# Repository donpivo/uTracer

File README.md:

Project description: https://retronics.no/tag/utracer/

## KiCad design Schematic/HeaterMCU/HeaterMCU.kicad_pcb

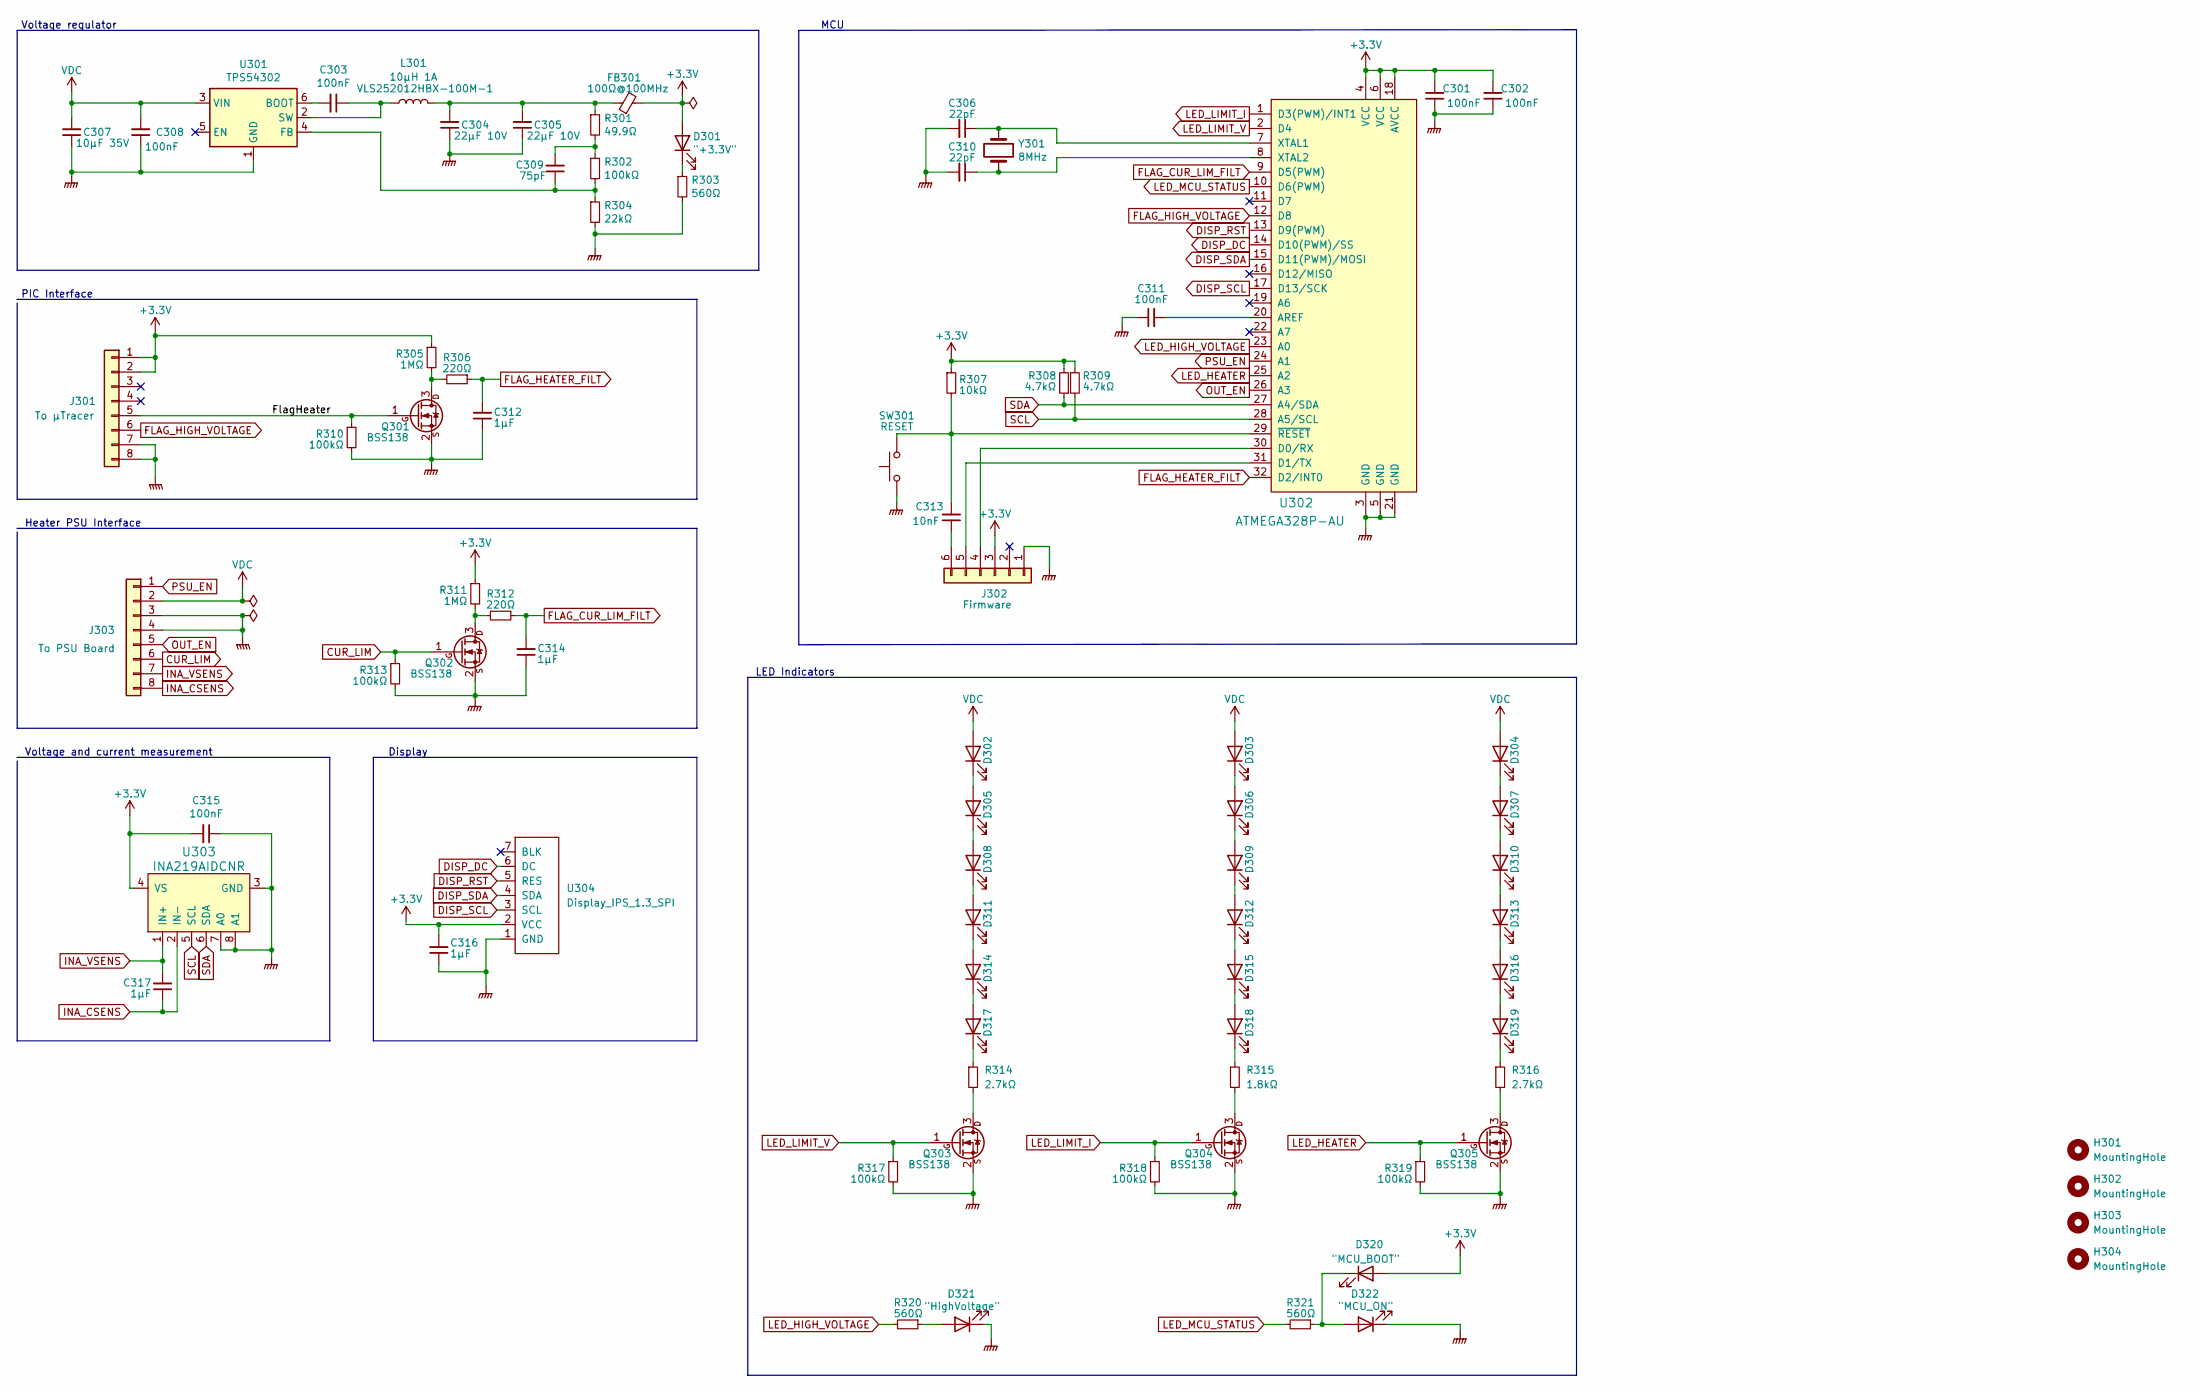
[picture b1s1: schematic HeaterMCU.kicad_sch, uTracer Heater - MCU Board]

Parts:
C301, C302, C303, C308, C311, C315: 100nF; C_0603_1608Metric_Pad1.08x0.95mm_HandSolder
C304, C305: 22µF 10V; C_0603_1608Metric_Pad1.08x0.95mm_HandSolder
C306, C310: 22pF; C_0603_1608Metric_Pad1.08x0.95mm_HandSolder
C307: 10µF 35V; C_0603_1608Metric_Pad1.08x0.95mm_HandSolder
C309: 75pF; C_0603_1608Metric_Pad1.08x0.95mm_HandSolder
C312, C314, C316, C317: 1µF; C_0603_1608Metric_Pad1.08x0.95mm_HandSolder
C313: 10nF; C_0603_1608Metric_Pad1.08x0.95mm_HandSolder
D301: "+3.3V"; LED_0603_1608Metric_Pad1.05x0.95mm_HandSolder
D302, D305, D308, D311, D314, D317: "Voltage limit"; LED_0603_1608Metric_Pad1.05x0.95mm_HandSolder
D303, D306, D309, D312, D315, D318: "Current limit"; LED_0603_1608Metric_Pad1.05x0.95mm_HandSolder
D304, D307, D310, D313, D316, D319: "Heater"; LED_0603_1608Metric_Pad1.05x0.95mm_HandSolder
D320: "MCU_BOOT"; LED_0603_1608Metric_Pad1.05x0.95mm_HandSolder
D321: "HighVoltage"; LED_0603_1608Metric_Pad1.05x0.95mm_HandSolder
D322: "MCU_ON"; LED_0603_1608Metric_Pad1.05x0.95mm_HandSolder
FB301: 100Ω@100MHz; L_0603_1608Metric_Pad1.05x0.95mm_HandSolder
H301, H302, H303, H304: MountingHole; MountingHole_3.2mm_M3
J301: To µTracer; 0527450897
J302: Firmware; PinHeader_1x06_P2.54mm_Vertical
J303: To PSU Board; PinHeader_1x08_P2.54mm_Vertical
L301: 10µH 1A; L_Taiyo-Yuden_NR-20xx_HandSoldering
Q301, Q302, Q303, Q304, Q305: BSS138; SOT-23
R301: 49.9Ω; R_0603_1608Metric_Pad0.98x0.95mm_HandSolder
R302, R310, R313, R317, R318, R319: 100kΩ; R_0603_1608Metric_Pad0.98x0.95mm_HandSolder
R303, R320, R321: 560Ω; R_0603_1608Metric_Pad0.98x0.95mm_HandSolder
R304: 22kΩ; R_0603_1608Metric_Pad0.98x0.95mm_HandSolder
R305, R311: 1MΩ; R_0603_1608Metric_Pad0.98x0.95mm_HandSolder
R306, R312: 220Ω; R_0603_1608Metric_Pad0.98x0.95mm_HandSolder
R307: 10kΩ; R_0603_1608Metric_Pad0.98x0.95mm_HandSolder
R308, R309: 4.7kΩ; R_0603_1608Metric_Pad0.98x0.95mm_HandSolder
R314, R316: 2.7kΩ; R_0603_1608Metric_Pad0.98x0.95mm_HandSolder
R315: 1.8kΩ; R_0603_1608Metric_Pad0.98x0.95mm_HandSolder
SW301: RESET; Tactile_sw_SMD_side_01
U301: TPS54302; SOT-23-6_Handsoldering
U302: ATMEGA328P-AU; TQFP-32_7x7mm
U303: INA219AIDCNR; SOT-23-8_Handsoldering; MPN INA219AIDCNR; Digi-Key_PN 296-23770-1-ND
U304: Display_IPS_1.3_SPI
Y301: 8MHz; Crystal_SMD_HC49-SD

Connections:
+3V3: C301.2, C302.2, C315.2, C316.2, D301.2 (A), D320.2 (A), FB301.2, J301.1, J301.2, J302.3, R305.1, R307.1, R308.2, R309.1, R311.1, U302.4 (VCC), U302.6 (VCC), U302.18 (AVCC), U303.4 (VS), U304.2 (VCC)
/FlagHeater: J301.5, Q301.1 (G), R310.1
CUR_LIM: J303.6, Q302.1 (G), R313.1
DISP_DC: U302.14 (D10(PWM)/SS), U304.6 (DC)
DISP_RST: U302.13 (D9(PWM)), U304.5 (RES)
DISP_SCL: U302.17 (D13/SCK), U304.3 (SCL)
DISP_SDA: U302.15 (D11(PWM)/MOSI), U304.4 (SDA)
FLAG_CUR_LIM_FILT: C314.2, R312.1, U302.9 (D5(PWM))
FLAG_HEATER_FILT: C312.2, R306.1, U302.32 (D2/INT0)
FLAG_HIGH_VOLTAGE: J301.6, U302.12 (D8)
GNDPWR: C301.1, C302.1, C304.1, C305.1, C306.2, C307.1, C308.1, C310.2, C311.1, C312.1, C314.1, C315.1, C316.1, D321.1 (K), D322.1 (K), J301.7, J301.8, J302.1, J303.3, J303.4, Q301.2 (S), Q302.2 (S), Q303.2 (S), Q304.2 (S), Q305.2 (S), R303.2, R304.2, R310.2, R313.2, R317.2, R318.2, R319.2, SW301.1, U301.1 (GND), U302.3 (GND), U302.5 (GND), U302.21 (GND), U303.3 (GND), U303.7 (A0), U303.8 (A1), U304.1 (GND)
INA_CSENS: C317.1, J303.8, U303.2 (IN-)
INA_VSENS: C317.2, J303.7, U303.1 (IN+)
LED_HEATER: Q305.1 (G), R319.1, U302.25 (A2)
LED_HIGH_VOLTAGE: R320.2, U302.23 (A0)
LED_LIMIT_I: Q304.1 (G), R318.1, U302.1 (D3(PWM)/INT1)
LED_LIMIT_V: Q303.1 (G), R317.1, U302.2 (D4)
LED_MCU_STATUS: R321.2, U302.10 (D6(PWM))
unnamed: C303.1, L301.1, U301.2 (SW)
unnamed: C303.2, U301.6 (BOOT)
unnamed: C304.2, C305.2, FB301.1, L301.2, R301.1
unnamed: C306.1, U302.7 (XTAL1), Y301.1
unnamed: C309.1, R302.2, R304.1, U301.4 (FB)
unnamed: C309.2, R301.2, R302.1
unnamed: C310.1, U302.8 (XTAL2), Y301.2
unnamed: C311.2, U302.20 (AREF)
unnamed: C313.1, J302.6
unnamed: C313.2, R307.2, SW301.2, U302.29 (~RESET)
unnamed: D301.1 (K), R303.1
unnamed: D302.1 (K), D305.2 (A)
unnamed: D303.1 (K), D306.2 (A)
unnamed: D304.1 (K), D307.2 (A)
unnamed: D305.1 (K), D308.2 (A)
unnamed: D306.1 (K), D309.2 (A)
unnamed: D307.1 (K), D310.2 (A)
unnamed: D308.1 (K), D311.2 (A)
unnamed: D309.1 (K), D312.2 (A)
unnamed: D310.1 (K), D313.2 (A)
unnamed: D311.1 (K), D314.2 (A)
unnamed: D312.1 (K), D315.2 (A)
unnamed: D313.1 (K), D316.2 (A)
unnamed: D314.1 (K), D317.2 (A)
unnamed: D315.1 (K), D318.2 (A)
unnamed: D316.1 (K), D319.2 (A)
unnamed: D317.1 (K), R314.1
unnamed: D318.1 (K), R315.1
unnamed: D319.1 (K), R316.1
unnamed: D320.1 (K), D322.2 (A), R321.1
unnamed: D321.2 (A), R320.1
unnamed: J302.4, U302.30 (D0/RX)
unnamed: J302.5, U302.31 (D1/TX)
unnamed: Q301.3 (D), R305.2, R306.2
unnamed: Q302.3 (D), R311.2, R312.2
unnamed: Q303.3 (D), R314.2
unnamed: Q304.3 (D), R315.2
unnamed: Q305.3 (D), R316.2
OUT_EN: J303.5, U302.26 (A3)
PSU_EN: J303.1, U302.24 (A1)
SCL: R309.2, U302.28 (A5/SCL), U303.5 (SCL)
SDA: R308.1, U302.27 (A4/SDA), U303.6 (SDA)
VDC: C307.2, C308.2, D302.2 (A), D303.2 (A), D304.2 (A), J303.2, U301.3 (VIN)

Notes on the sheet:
Voltage regulator
Heater PSU Interface
Display
PIC Interface
LED Indicators
MCU
Voltage and current measurement

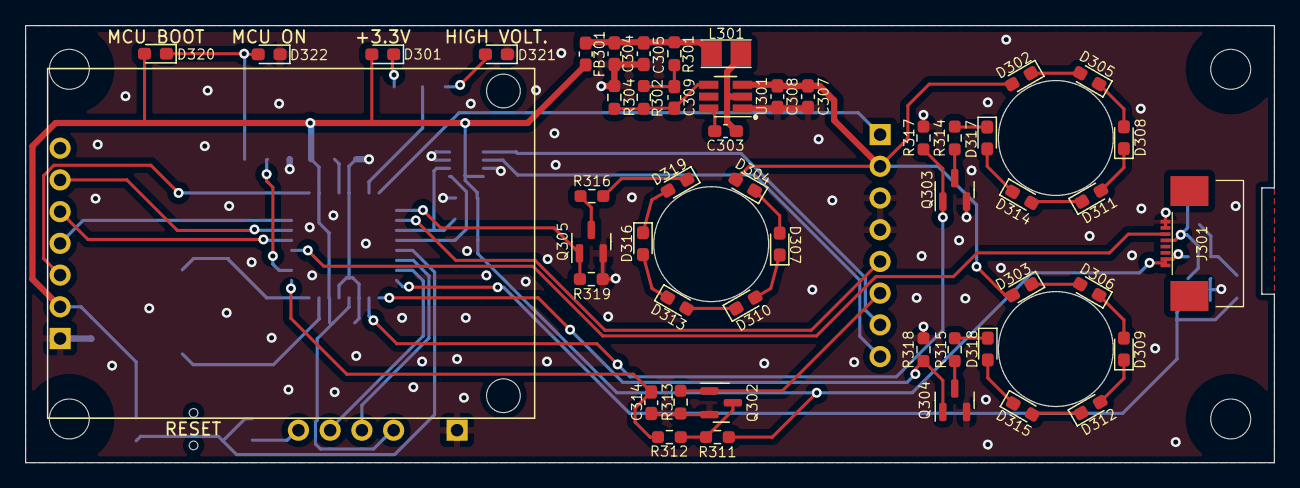
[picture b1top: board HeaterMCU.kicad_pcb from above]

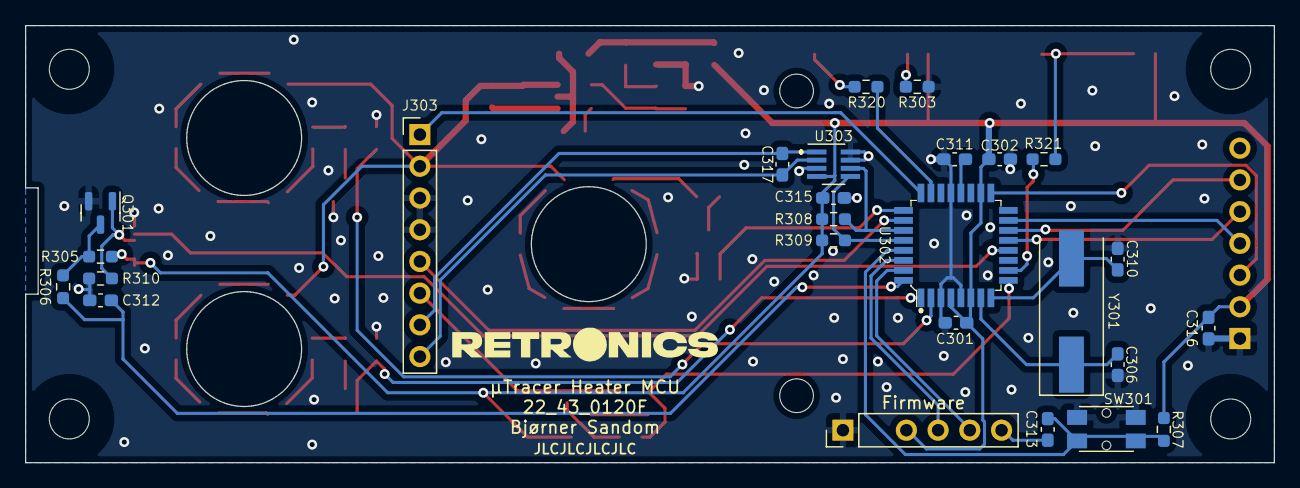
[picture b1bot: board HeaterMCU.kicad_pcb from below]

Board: 2 copper layers, 100.0 x 35.0 mm, 80 parts (26 on the bottom side), 61 nets.

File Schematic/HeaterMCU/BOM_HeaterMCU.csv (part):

"Source:","C:\Users\bjorn\OneDrive\Projects\µTracer\Schematic\HeaterMCU\HeaterMCU.kicad_sch"
"Date:","Fri May 12 07:43:41 2023"
"Tool:","Eeschema (6.0.11)"
"Generator:","C:\Program Files\KiCad\6.0\bin\scripting\plugins/bom_csv_grouped_by_value.py"
"Component Count:","80"

"Individual Components:"

"Item","Qty","Reference(s)","Value","LibPart","Footprint","Datasheet","Category","Comments","DK_Datasheet_Link","DK_Detail_Page","Description","Digi-Key_PN","Family","MPN","Manufacturer","Status"
"","","C301","100nF","Device:C_Small","Capacitor_SMD:C_0603_1608Metric_Pad1.08x0.95mm_HandSolder","~","","","","","","","","","",""
"","","C302","100nF","Device:C_Small","Capacitor_SMD:C_0603_1608Metric_Pad1.08x0.95mm_HandSolder","~","","","","","","","","","",""
"","","C303","100nF","Device:C_Small","Capacitor_SMD:C_0603_1608Metric_Pad1.08x0.95mm_HandSolder","~","","","","","","","","","",""
"","","C304","22µF 10V","Device:C_Small","Capacitor_SMD:C_0603_1608Metric_Pad1.08x0.95mm_HandSolder","~","","","","","","","","","",""
"","","C305","22µF 10V","Device:C_Small","Capacitor_SMD:C_0603_1608Metric_Pad1.08x0.95mm_HandSolder","~","","","","","","","","","",""
"","","C306","22pF","Device:C_Small","Capacitor_SMD:C_0603_1608Metric_Pad1.08x0.95mm_HandSolder","~","","","","","","","","","",""
"","","C307","10µF 35V","Device:C_Small","Capacitor_SMD:C_0603_1608Metric_Pad1.08x0.95mm_HandSolder","~","","","","","","","","","",""
"","","C308","100nF","Device:C_Small","Capacitor_SMD:C_0603_1608Metric_Pad1.08x0.95mm_HandSolder","~","","","","","","","","","",""
"","","C309","75pF","Device:C_Small","Capacitor_SMD:C_0603_1608Metric_Pad1.08x0.95mm_HandSolder","~","","","","","","","","","",""
"","","C310","22pF","Device:C_Small","Capacitor_SMD:C_0603_1608Metric_Pad1.08x0.95mm_HandSolder","~","","","","","","","","","",""
"","","C311","100nF","Device:C_Small","Capacitor_SMD:C_0603_1608Metric_Pad1.08x0.95mm_HandSolder","~","","","","","","","","","",""
"","","C312","1µF","Device:C_Small","Capacitor_SMD:C_0603_1608Metric_Pad1.08x0.95mm_HandSolder","~","","","","","","","","","",""
"","","C313","10nF","Device:C_Small","Capacitor_SMD:C_0603_1608Metric_Pad1.08x0.95mm_HandSolder","~","","","","","","","","","",""
"","","C314","1µF","Device:C_Small","Capacitor_SMD:C_0603_1608Metric_Pad1.08x0.95mm_HandSolder","~","","","","","","","","","",""
"","","C315","100nF","Device:C_Small","Capacitor_SMD:C_0603_1608Metric_Pad1.08x0.95mm_HandSolder","~","","","","","","","","","",""
"","","C316","1µF","Device:C_Small","Capacitor_SMD:C_0603_1608Metric_Pad1.08x0.95mm_HandSolder","~","","","","","","","","","",""
"","","C317","1µF","Device:C_Small","Capacitor_SMD:C_0603_1608Metric_Pad1.08x0.95mm_HandSolder","~","","","","","","","","","",""
"","","D301","""+3.3V""","Device:LED","LED_SMD:LED_0603_1608Metric_Pad1.05x0.95mm_HandSolder","~","","","","","","","","","",""
"","","D302","""Voltage limit""","Device:LED","LED_SMD:LED_0603_1608Metric_Pad1.05x0.95mm_HandSolder","~","","","","","","","","","",""
"","","D303","""Current limit""","Device:LED","LED_SMD:LED_0603_1608Metric_Pad1.05x0.95mm_HandSolder","~","","","","","","","","","",""
"","","D304","""Heater""","Device:LED","LED_SMD:LED_0603_1608Metric_Pad1.05x0.95mm_HandSolder","~","","","","","","","","","",""
"","","D305","""Voltage limit""","Device:LED","LED_SMD:LED_0603_1608Metric_Pad1.05x0.95mm_HandSolder","~","","","","","","","","","",""
"","","D306","""Current limit""","Device:LED","LED_SMD:LED_0603_1608Metric_Pad1.05x0.95mm_HandSolder","~","","","","","","","","","",""
"","","D307","""Heater""","Device:LED","LED_SMD:LED_0603_1608Metric_Pad1.05x0.95mm_HandSolder","~","","","","","","","","","",""
"","","D308","""Voltage limit""","Device:LED","LED_SMD:LED_0603_1608Metric_Pad1.05x0.95mm_HandSolder","~","","","","","","","","","",""
"","","D309","""Current limit""","Device:LED","LED_SMD:LED_0603_1608Metric_Pad1.05x0.95mm_HandSolder","~","","","","","","","","","",""
"","","D310","""Heater""","Device:LED","LED_SMD:LED_0603_1608Metric_Pad1.05x0.95mm_HandSolder","~","","","","","","","","","",""
"","","D311","""Voltage limit""","Device:LED","LED_SMD:LED_0603_1608Metric_Pad1.05x0.95mm_HandSolder","~","","","","","","","","","",""
"","","D312","""Current limit""","Device:LED","LED_SMD:LED_0603_1608Metric_Pad1.05x0.95mm_HandSolder","~","","","","","","","","","",""
"","","D313","""Heater""","Device:LED","LED_SMD:LED_0603_1608Metric_Pad1.05x0.95mm_HandSolder","~","","","","","","","","","",""
"","","D314","""Voltage limit""","Device:LED","LED_SMD:LED_0603_1608Metric_Pad1.05x0.95mm_HandSolder","~","","","","","","","","","",""
"","","D315","""Current limit""","Device:LED","LED_SMD:LED_0603_1608Metric_Pad1.05x0.95mm_HandSolder","~","","","","","","","","","",""
"","","D316","""Heater""","Device:LED","LED_SMD:LED_0603_1608Metric_Pad1.05x0.95mm_HandSolder","~","","","","","","","","","",""
"","","D317","""Voltage limit""","Device:LED","LED_SMD:LED_0603_1608Metric_Pad1.05x0.95mm_HandSolder","~","","","","","","","","","",""
"","","D318","""Current limit""","Device:LED","LED_SMD:LED_0603_1608Metric_Pad1.05x0.95mm_HandSolder","~","","","","","","","","","",""
"","","D319","""Heater""","Device:LED","LED_SMD:LED_0603_1608Metric_Pad1.05x0.95mm_HandSolder","~","","","","","","","","","",""
"","","D320","""MCU_BOOT""","Device:LED","LED_SMD:LED_0603_1608Metric_Pad1.05x0.95mm_HandSolder","~","","","","","","","","","",""
"","","D321","""HighVoltage""","Device:LED","LED_SMD:LED_0603_1608Metric_Pad1.05x0.95mm_HandSolder","~","","","","","","","","","",""
"","","D322","""MCU_ON""","Device:LED","LED_SMD:LED_0603_1608Metric_Pad1.05x0.95mm_HandSolder","~","","","","","","","","","",""
"","","FB301","100Ω@100MHz","Device:FerriteBead_Small","Inductor_SMD:L_0603_1608Metric_Pad1.05x0.95mm_HandSolder","~","","","","","","","","","",""
"","","H301","MountingHole","Mechanical:MountingHole","MountingHole:MountingHole_3.2mm_M3","~","","","","","","","","","",""
"","","H302","MountingHole","Mechanical:MountingHole","MountingHole:MountingHole_3.2mm_M3","~","","","","","","","","","",""
"","","H303","MountingHole","Mechanical:MountingHole","MountingHole:MountingHole_3.2mm_M3","~","","","","","","","","","",""
"","","H304","MountingHole","Mechanical:MountingHole","MountingHole:MountingHole_3.2mm_M3","~","","","","","","","","","",""
"","","J301","To µTracer","Connector_Generic:Conn_01x08","myDevices:0527450897","~","","","","","","","","","",""
"","","J302","Firmware","Connector_Generic:Conn_01x06","Connector_PinHeader_2.54mm:PinHeader_1x06_P2.54mm_Vertical","~","","","","","","","","","",""
"","","J303","To PSU Board","Connector_Generic:Conn_01x08","Connector_PinHeader_2.54mm:PinHeader_1x08_P2.54mm_Vertical","~","","","","","","","","","",""
"","","L301","10µH 1A","Device:L","Inductor_SMD:L_Taiyo-Yuden_NR-20xx_HandSoldering","~","","VLS252012HBX-100M-1","","","","","","","",""
"","","Q301","BSS138","myDevices:BSS138","Package_TO_SOT_SMD:SOT-23","https://www.fairchildsemi.com/datasheets/BS/BSS138.pdf","","","","","","","","","",""
"","","Q302","BSS138","myDevices:BSS138","Package_TO_SOT_SMD:SOT-23","https://www.fairchildsemi.com/datasheets/BS/BSS138.pdf","","","","","","","","","",""
"","","Q303","BSS138","myDevices:BSS138","Package_TO_SOT_SMD:SOT-23","https://www.fairchildsemi.com/datasheets/BS/BSS138.pdf","","","","","","","","","",""
"","","Q304","BSS138","myDevices:BSS138","Package_TO_SOT_SMD:SOT-23","https://www.fairchildsemi.com/datasheets/BS/BSS138.pdf","","","","","","","","","",""
"","","Q305","BSS138","myDevices:BSS138","Package_TO_SOT_SMD:SOT-23","https://www.fairchildsemi.com/datasheets/BS/BSS138.pdf","","","","","","","","","",""
"","","R301","49.9Ω","Device:R_Small","Resistor_SMD:R_0603_1608Metric_Pad0.98x0.95mm_HandSolder","~","","","","","","","","","",""
"","","R302","100kΩ","Device:R_Small","Resistor_SMD:R_0603_1608Metric_Pad0.98x0.95mm_HandSolder","~","","","","","","","","","",""
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
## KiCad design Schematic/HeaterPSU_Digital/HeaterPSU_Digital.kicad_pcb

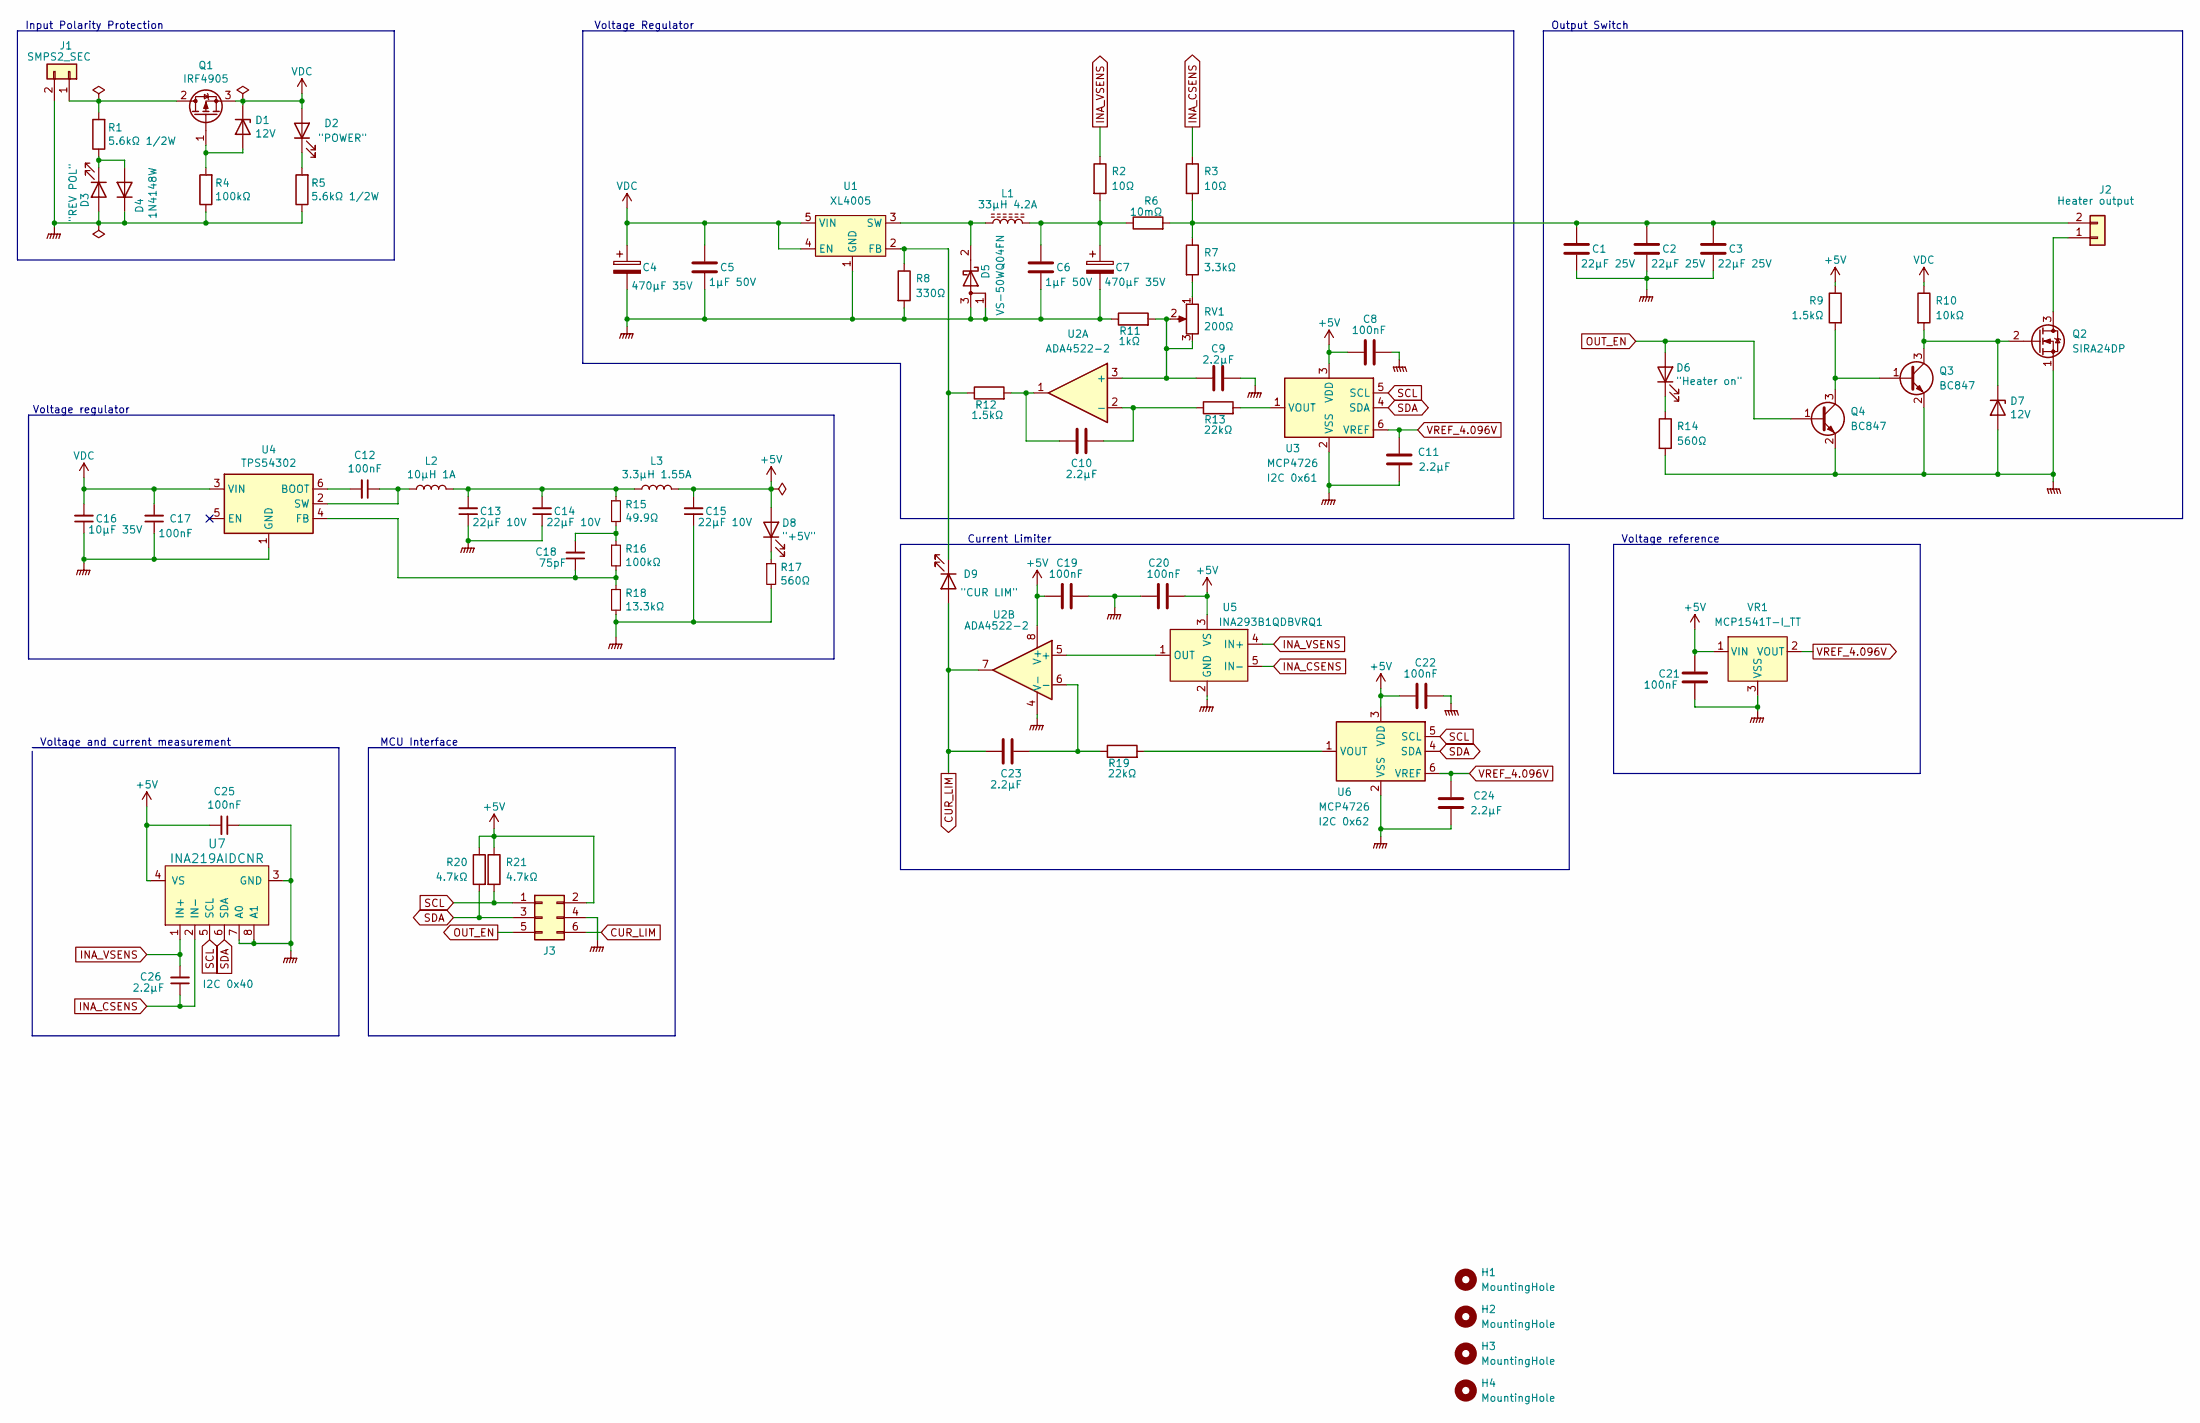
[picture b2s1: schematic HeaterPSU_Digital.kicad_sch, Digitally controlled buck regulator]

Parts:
C1, C2, C3: 22µF 25V; C_0805_2012Metric_Pad1.18x1.45mm_HandSolder
C4, C7: 470µF 35V; CP_Elec_8x10
C5, C6: 1µF 50V; C_0805_2012Metric_Pad1.18x1.45mm_HandSolder
C8, C12, C17, C19, C20, C21, C22, C25: 100nF; C_0603_1608Metric_Pad1.08x0.95mm_HandSolder
C9, C10, C11, C23, C24, C26: 2.2µF; C_0603_1608Metric_Pad1.08x0.95mm_HandSolder
C13, C14, C15: 22µF 10V; C_0603_1608Metric_Pad1.08x0.95mm_HandSolder
C16: 10µF 35V; C_0603_1608Metric_Pad1.08x0.95mm_HandSolder
C18: 75pF; C_0603_1608Metric_Pad1.08x0.95mm_HandSolder
D1, D7: 12V; D_SOD-123
D2: "POWER"; LED_0603_1608Metric_Pad1.05x0.95mm_HandSolder
D3: "REV POL"; LED_0603_1608Metric_Pad1.05x0.95mm_HandSolder
D4: 1N4148W; D_SOD-123
D5: VS-50WQ04FN; TO-252-2
D6: "Heater on"; LED_0603_1608Metric_Pad1.05x0.95mm_HandSolder
D8: "+5V"; LED_0603_1608Metric_Pad1.05x0.95mm_HandSolder
D9: "CUR LIM"; LED_0603_1608Metric_Pad1.05x0.95mm_HandSolder
H1, H2, H3, H4: MountingHole; MountingHole_3.2mm_M3
J1: SMPS2_SEC; TerminalBlock_LCSC_P5.08mm
J2: Heater output; TerminalBlock_LCSC_P5.08mm
J3: Conn_01x06; PinSocket_2x03_P1.27mm_Vertical_SMD
L1: 33µH 4.2A; L_12x12mm_H8mm
L2: 10µH 1A; L_Taiyo-Yuden_NR-20xx_HandSoldering
L3: 3.3µH 1.55A; L_Taiyo-Yuden_NR-20xx_HandSoldering
Q1: IRF4905; TO-263-2
Q2: SIRA24DP; SIRA24DP-T1-GE3
Q3, Q4: BC847; SOT-23
R1, R5: 5.6kΩ 1/2W; R_1210_3225Metric_Pad1.30x2.65mm_HandSolder
R2, R3: 10Ω; R_0603_1608Metric_Pad0.98x0.95mm_HandSolder
R4: 100kΩ; R_0805_2012Metric_Pad1.20x1.40mm_HandSolder
R6: 10mΩ; R_2512_6332Metric_Pad1.40x3.35mm_HandSolder
R7: 3.3kΩ; R_0603_1608Metric_Pad0.98x0.95mm_HandSolder
R8: 330Ω; R_0603_1608Metric_Pad0.98x0.95mm_HandSolder
R9, R12: 1.5kΩ; R_0603_1608Metric_Pad0.98x0.95mm_HandSolder
R10: 10kΩ; R_0603_1608Metric_Pad0.98x0.95mm_HandSolder
R11: 1kΩ; R_0603_1608Metric_Pad0.98x0.95mm_HandSolder
R13, R19: 22kΩ; R_0603_1608Metric_Pad0.98x0.95mm_HandSolder
R14, R17: 560Ω; R_0603_1608Metric_Pad0.98x0.95mm_HandSolder
R15: 49.9Ω; R_0603_1608Metric_Pad0.98x0.95mm_HandSolder
R16: 100kΩ; R_0603_1608Metric_Pad0.98x0.95mm_HandSolder
R18: 13.3kΩ; R_0603_1608Metric_Pad0.98x0.95mm_HandSolder
R20, R21: 4.7kΩ; R_0603_1608Metric_Pad0.98x0.95mm_HandSolder
RV1: 200Ω; Potentiometer_TT_35W
U1: XL4005; TO-263-5_TabPin3
U2: ADA4522-2; SOIC-8_3.9x4.9mm_P1.27mm
U3, U6: MCP4726; SOT-23-6
U4: TPS54302; SOT-23-6_Handsoldering
U5: INA293B1QDBVRQ1; SOT-23-5_HandSoldering
U7: INA219AIDCNR; SOT-23-8_Handsoldering; MPN INA219AIDCNR; Digi-Key_PN 296-23770-1-ND
VR1: MCP1541T-I_TT; SOT-23-3; MPN MCP1541T-I/TT; Digi-Key_PN MCP1541T-I/TTCT-ND

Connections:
+5V: C8.2, C15.2, C19.2, C20.2, C21.2, C22.2, C25.2, D8.2 (A), J3.2, L3.2, R9.1, R20.1, R21.1, U2.8 (V+), U3.3 (VDD), U5.3 (VS), U6.3 (VDD), U7.4 (VS), VR1.1 (VIN)
CUR_LIM: C23.1, D9.2 (A), J3.6, U2.7
INA_CSENS: C26.1, R3.1, U5.5 (IN-), U7.2 (IN-)
INA_VSENS: C26.2, R2.1, U5.4 (IN+), U7.1 (IN+)
unnamed: C1.1, C2.1, C3.1, J2.2, R3.2, R6.2, R7.1
unnamed: C6.1, C7.1, L1.2, R2.2, R6.1
unnamed: C9.1, R11.2, RV1.2, RV1.3, U2.3 (+)
unnamed: C10.1, R12.2, U2.1
unnamed: C10.2, R13.1, U2.2 (-)
unnamed: C12.1, L2.1, U4.2 (SW)
unnamed: C12.2, U4.6 (BOOT)
unnamed: C13.2, C14.2, L2.2, L3.1, R15.1
unnamed: C18.1, R16.2, R18.1, U4.4 (FB)
unnamed: C18.2, R15.2, R16.1
unnamed: C23.2, R19.1, U2.6 (-)
unnamed: D1.2 (A), Q1.1 (G), R4.2
unnamed: D2.1 (K), R5.2
unnamed: D3.1 (K), D4.2 (A), R1.1
unnamed: D5.2 (K), L1.1, U1.3 (SW)
unnamed: D6.1 (K), R14.1
unnamed: D8.1 (K), R17.1
unnamed: D9.1 (K), R8.1, R12.1, U1.2 (FB)
unnamed: J1.1, Q1.2 (D), R1.2
unnamed: J2.1, Q2.3 (D)
unnamed: Q3.1 (B), Q4.3 (C), R9.2
unnamed: R7.2, RV1.1
unnamed: D7.1 (K), Q2.2 (G), Q3.3 (C), R10.2
unnamed: R13.2, U3.1 (VOUT)
unnamed: R19.2, U6.1 (VOUT)
unnamed: U2.5 (+), U5.1 (OUT)
OUT_EN: D6.2 (A), J3.5, Q4.1 (B)
SCL: J3.1, R21.2, U3.5 (SCL), U6.5 (SCL), U7.5 (SCL)
SDA: J3.3, R20.2, U3.4 (SDA), U6.4 (SDA), U7.6 (SDA)
VDC: C4.1, C5.1, C16.2, C17.2, D1.1 (K), D2.2 (A), Q1.3 (S), R10.1, U1.4 (EN), U1.5 (VIN), U4.3 (VIN)
VREF_4.096V: C11.1, C24.1, U3.6 (VREF), U6.6 (VREF), VR1.2 (VOUT)

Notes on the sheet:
Voltage regulator
Output Switch
MCU Interface
Current Limiter
Voltage Regulator
Voltage and current measurement
Input Polarity Protection
Voltage reference

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
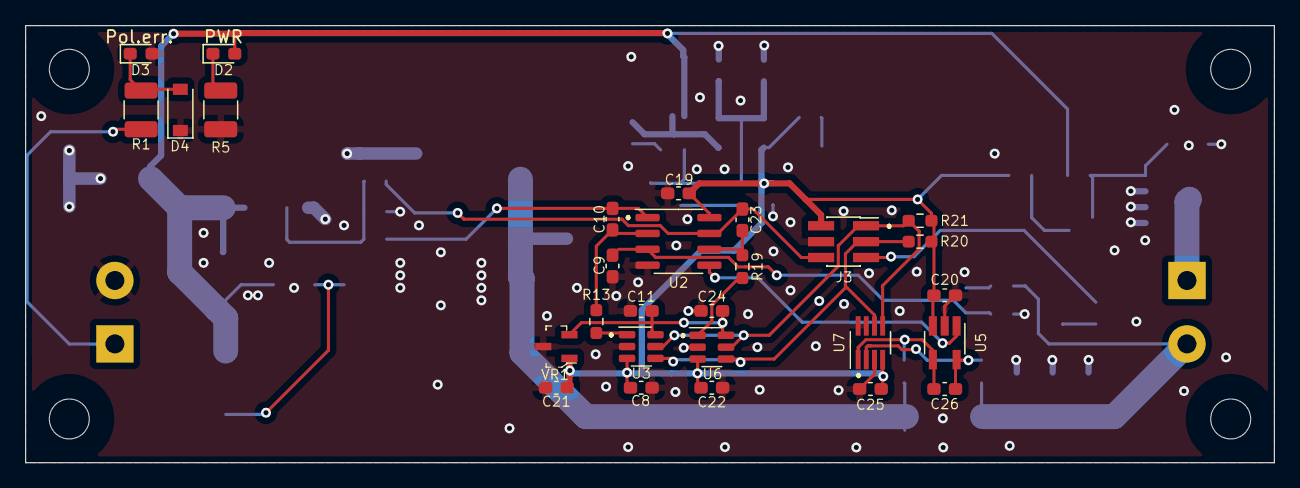
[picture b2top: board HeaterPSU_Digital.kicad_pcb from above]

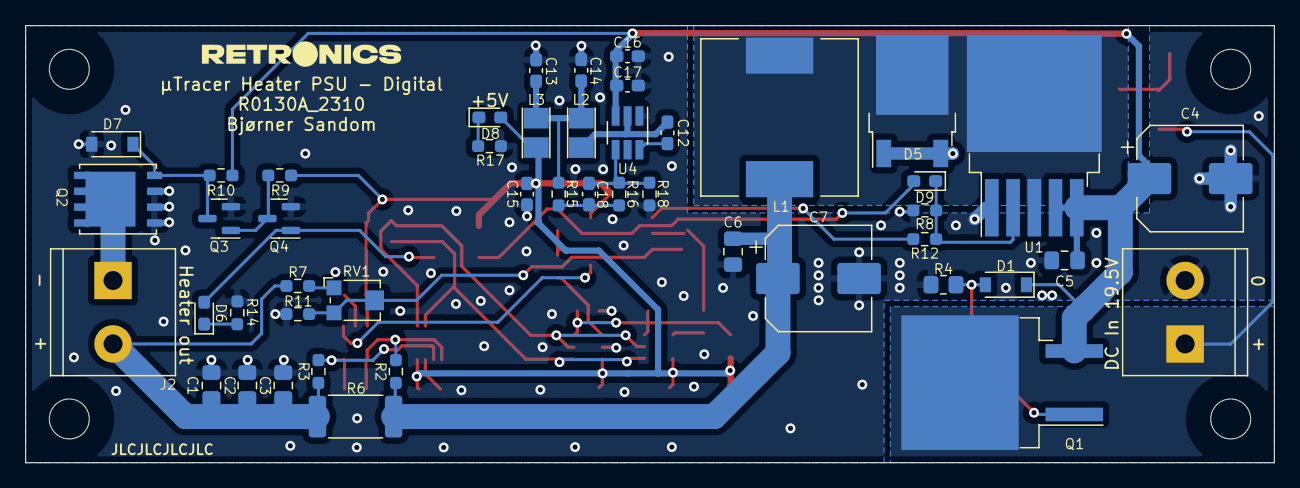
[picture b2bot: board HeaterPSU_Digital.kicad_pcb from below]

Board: 2 copper layers, 100.0 x 35.0 mm, 79 parts (47 on the bottom side), 36 nets.
